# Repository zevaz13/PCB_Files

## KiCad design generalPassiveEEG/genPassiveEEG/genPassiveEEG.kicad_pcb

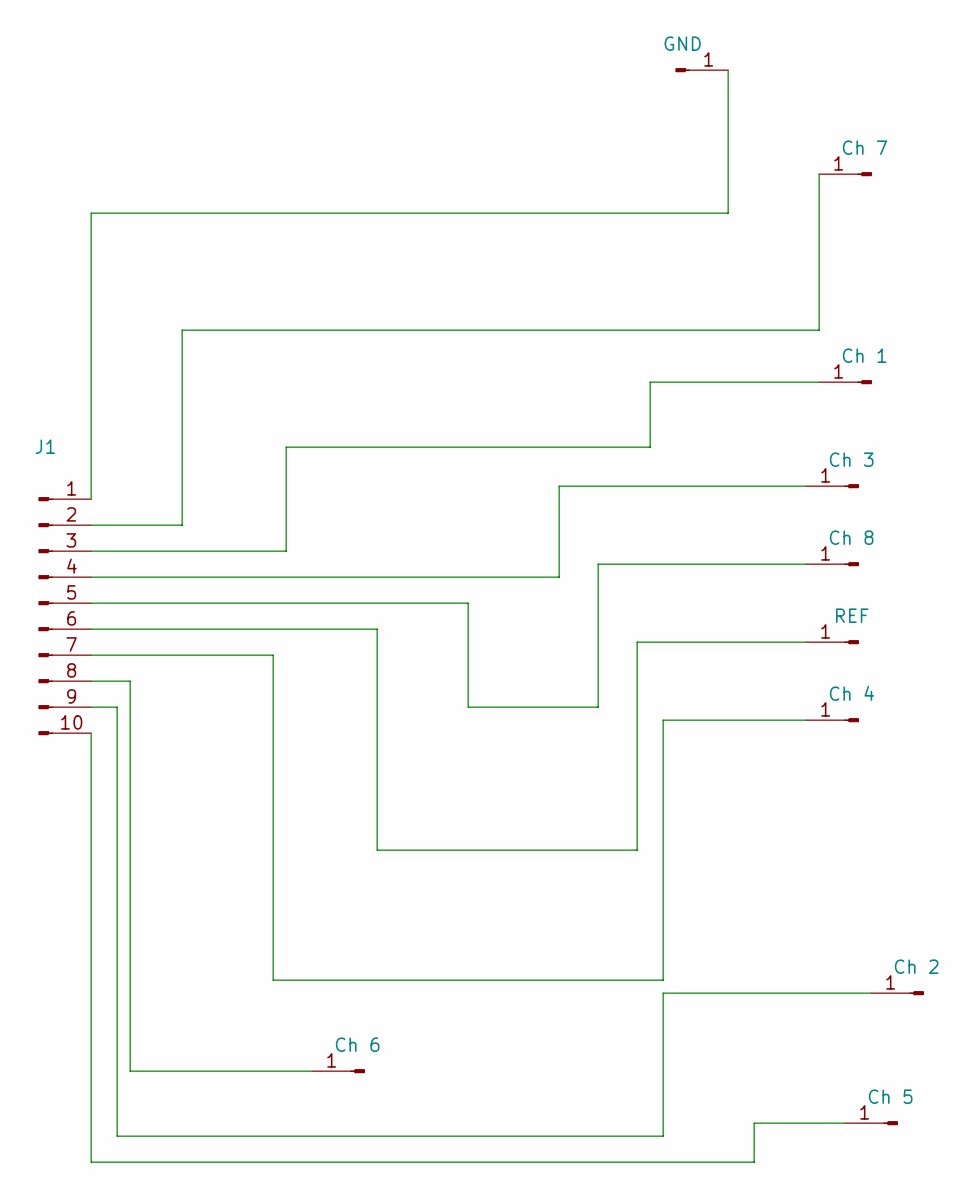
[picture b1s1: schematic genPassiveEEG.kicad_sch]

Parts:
J1: Conn_01x10_Pin; PinHeader_1x10_P2.54mm_Vertical
J2: Ch 7; PinHeader_1x01_P2.54mm_Vertical
J3: Ch 1; PinHeader_1x01_P2.54mm_Vertical
J4: Ch 3; PinHeader_1x01_P2.54mm_Vertical
J5: Ch 8; PinHeader_1x01_P2.54mm_Vertical
J6: REF; PinHeader_1x01_P2.54mm_Vertical
J7: Ch 4; PinHeader_1x01_P2.54mm_Vertical
J8: Ch 6; PinHeader_1x01_P2.54mm_Vertical
J9: Ch 2; PinHeader_1x01_P2.54mm_Vertical
J10: Ch 5; PinHeader_1x01_P2.54mm_Vertical
J12: GND; PinHeader_1x01_P2.54mm_Vertical

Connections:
unnamed: J1.1, J12.1
unnamed: J1.2, J2.1
unnamed: J1.3, J3.1
unnamed: J1.4, J4.1
unnamed: J1.5, J5.1
unnamed: J1.6, J6.1
unnamed: J1.7, J7.1
unnamed: J1.8, J8.1
unnamed: J1.9, J9.1
unnamed: J1.10, J10.1

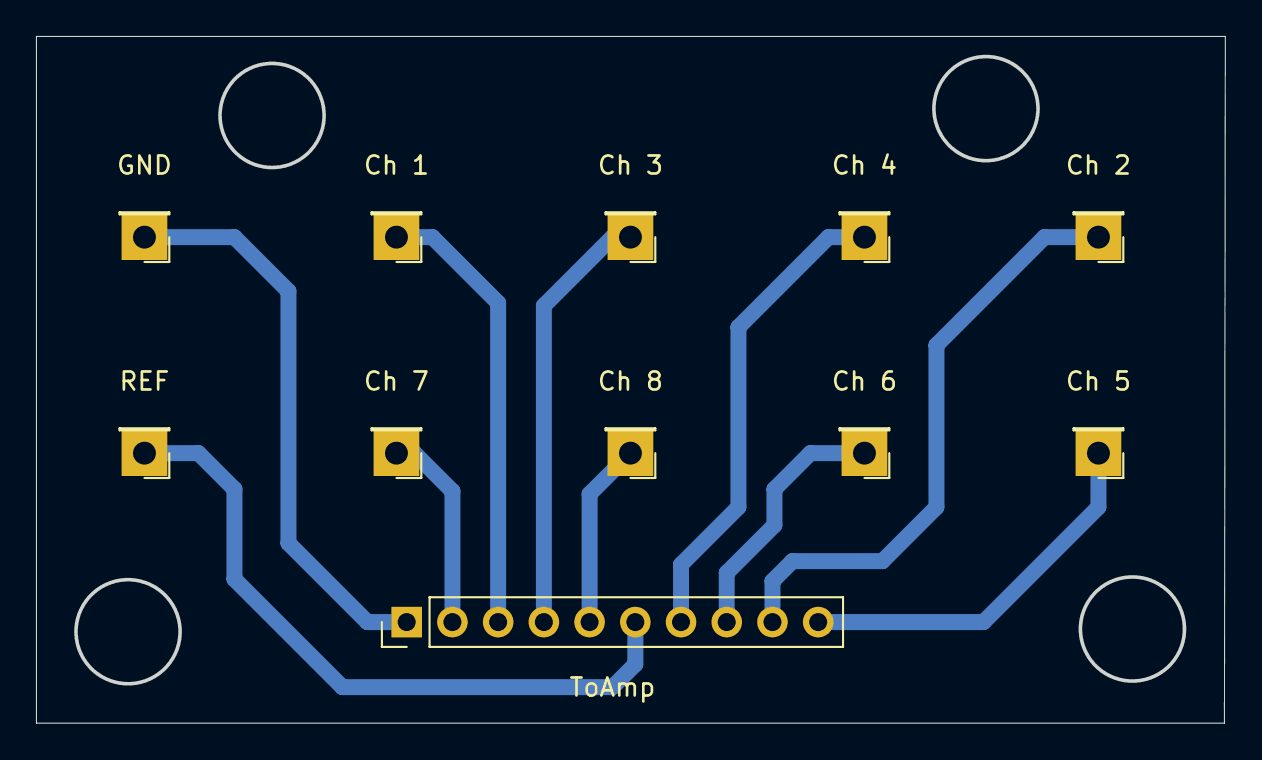
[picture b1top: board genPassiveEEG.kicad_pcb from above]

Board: 2 copper layers, 66.0 x 38.1 mm, 11 parts (0 on the bottom side), 10 nets.

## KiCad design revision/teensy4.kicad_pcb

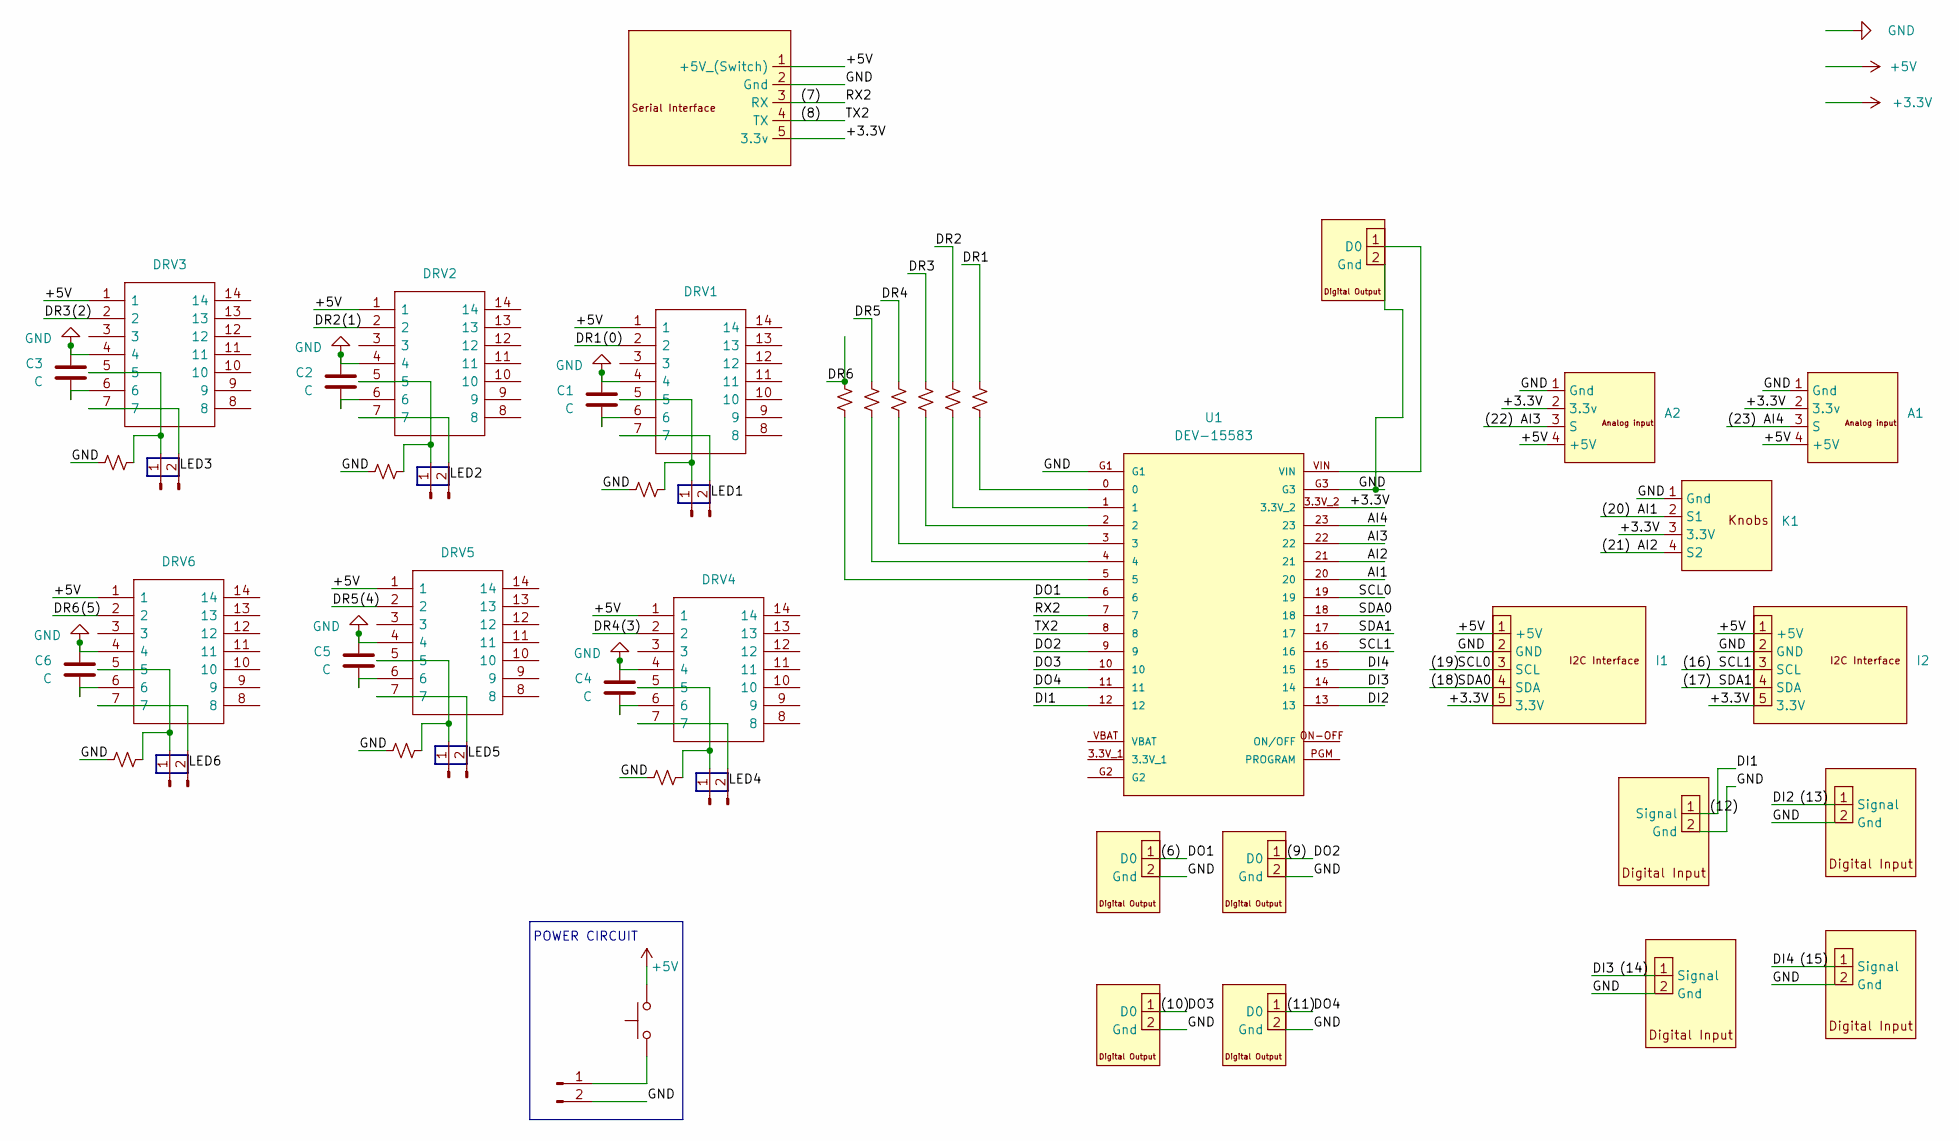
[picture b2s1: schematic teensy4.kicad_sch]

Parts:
A1, A2: FanPinHeader_1x04_P2.54mm_Vertical
C1, C2, C3, C4, C5, C6: C; C_Axial_L3.8mm_D2.6mm_P7.50mm_Horizontal
DI1, DI2, DI3, DI4: PhoenixContact_MSTBVA_2,5_2-G-5,08_1x02_P5.08mm_Vertical
DO1, DO2, DO3, DO4, DO5: PhoenixContact_MSTBVA_2,5_2-G-5,08_1x02_P5.08mm_Vertical
DRV1: DRV1; PA0186; Manufacturer_Part_Number PA0186; Mouser Part Number 910-PA0186
DRV2: DRV2; PA0186; Manufacturer_Part_Number PA0186; Mouser Part Number 910-PA0186
DRV3: DRV3; PA0186; Manufacturer_Part_Number PA0186; Mouser Part Number 910-PA0186
DRV4: DRV4; PA0186; Manufacturer_Part_Number PA0186; Mouser Part Number 910-PA0186
DRV5: DRV5; PA0186; Manufacturer_Part_Number PA0186; Mouser Part Number 910-PA0186
DRV6: DRV6; PA0186; Manufacturer_Part_Number PA0186; Mouser Part Number 910-PA0186
I1, I2: PinHeader_1x05_P2.54mm_Vertical
K1: FanPinHeader_1x04_P2.54mm_Vertical
L1, L2, L3, L4, L5, L6: Conn_01x02_Pin; TerminalBlock_MaiXu_MX126-5.0-02P_1x02_P5.00mm
Power1: Conn_01x02_Pin; TerminalBlock_MaiXu_MX126-5.0-02P_1x02_P5.00mm
RD1, RD2, RD3, RD4, RD5, RD6: R_Small_US; R_Axial_DIN0414_L11.9mm_D4.5mm_P15.24mm_Horizontal
RT0, RT1, RT2, RT3, RT4, RT5: R_Small_US; R_Axial_DIN0207_L6.3mm_D2.5mm_P10.16mm_Horizontal
S1: PinHeader_1x05_P2.54mm_Vertical
SW1: SW_Push; TerminalBlock_MaiXu_MX126-5.0-02P_1x02_P5.00mm
U1: DEV-15583; MODULE_DEV-15583

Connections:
+3.3V: A1.2 (3.3v), A2.2 (3.3v), I1.5 (3.3V), I2.5 (3.3V), K1.3 (3.3V), S1.5 (3.3v), U1.3.3V_2; also elsewhere on the board
+5V: A1.4 (+5V), A2.4 (+5V), DRV1.1, DRV2.1, DRV3.1, DRV4.1, DRV5.1, DRV6.1, I1.1 (+5V), I2.1 (+5V), S1.1 (+5V_(Switch)), SW1.2; also elsewhere on the board
/(0): DRV1.2, RT0.1
/(1): DRV2.2, RT1.1
/(2): DRV3.2, RT2.1
/(3): DRV4.2, RT3.1
/(4): DRV5.2, RT4.1
/(5): DRV6.2, RT5.1
/(6): DO1.1 (D0), U1.6
/(7): S1.3 (RX), U1.7
/(8): S1.4 (TX), U1.8
/(9): DO2.1 (D0), U1.9
/(10): DO3.1 (D0), U1.10
/(11): DO4.1 (D0), U1.11
/(12): DI1.1 (Signal), U1.12
/(13): DI2.1 (Signal), U1.13
/(14): DI3.1 (Signal), U1.14
/(15): DI4.1 (Signal), U1.15
/(16): I2.3 (SCL), U1.16; also elsewhere on the board
/(17): I2.4 (SDA), U1.17; also elsewhere on the board
/(18): I1.4 (SDA), U1.18; also elsewhere on the board
/(19): I1.3 (SCL), U1.19; also elsewhere on the board
/(20): K1.2 (S1), U1.20
/(21): K1.4 (S2), U1.21
/(22): A2.3 (S), U1.22
/(23): A1.3 (S), U1.23
GND: A1.1 (Gnd), A2.1 (Gnd), C1.1, C2.1, C3.1, C4.1, C5.1, C6.1, DI1.2 (Gnd), DI2.2 (Gnd), DI3.2 (Gnd), DI4.2 (Gnd), DO1.2 (Gnd), DO2.2 (Gnd), DO3.2 (Gnd), DO4.2 (Gnd), DO5.2 (Gnd), DRV1.4, DRV2.4, DRV3.4, DRV4.4, DRV5.4, DRV6.4, I1.2 (GND), I2.2 (GND), K1.1 (Gnd), Power1.2, RD1.1, RD2.1, RD3.1, RD4.1, RD5.1, RD6.1, S1.2 (Gnd), U1.G1, U1.G3; also elsewhere on the board
unnamed: C1.2, DRV1.6
unnamed: C2.2, DRV2.6
unnamed: C3.2, DRV3.6
unnamed: C4.2, DRV4.6
unnamed: C5.2, DRV5.6
unnamed: C6.2, DRV6.6
unnamed: DO5.1 (D0), U1.VIN
unnamed: DRV1.5, L1.1, RD1.2
unnamed: DRV1.7, L1.2
unnamed: DRV2.5, L2.1, RD2.2
unnamed: DRV2.7, L2.2
unnamed: DRV3.5, L3.1, RD3.2
unnamed: DRV3.7, L3.2
unnamed: DRV4.5, L4.1, RD4.2
unnamed: DRV4.7, L4.2
unnamed: DRV5.5, L5.1, RD5.2
unnamed: DRV5.7, L5.2
unnamed: DRV6.5, L6.1, RD6.2
unnamed: DRV6.7, L6.2
unnamed: Power1.1, SW1.1
unnamed: RT0.2, U1.0
unnamed: RT1.2, U1.1
unnamed: RT2.2, U1.2
unnamed: RT3.2, U1.3
unnamed: RT4.2, U1.4
unnamed: RT5.2, U1.5

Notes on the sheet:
POWER CIRCUIT

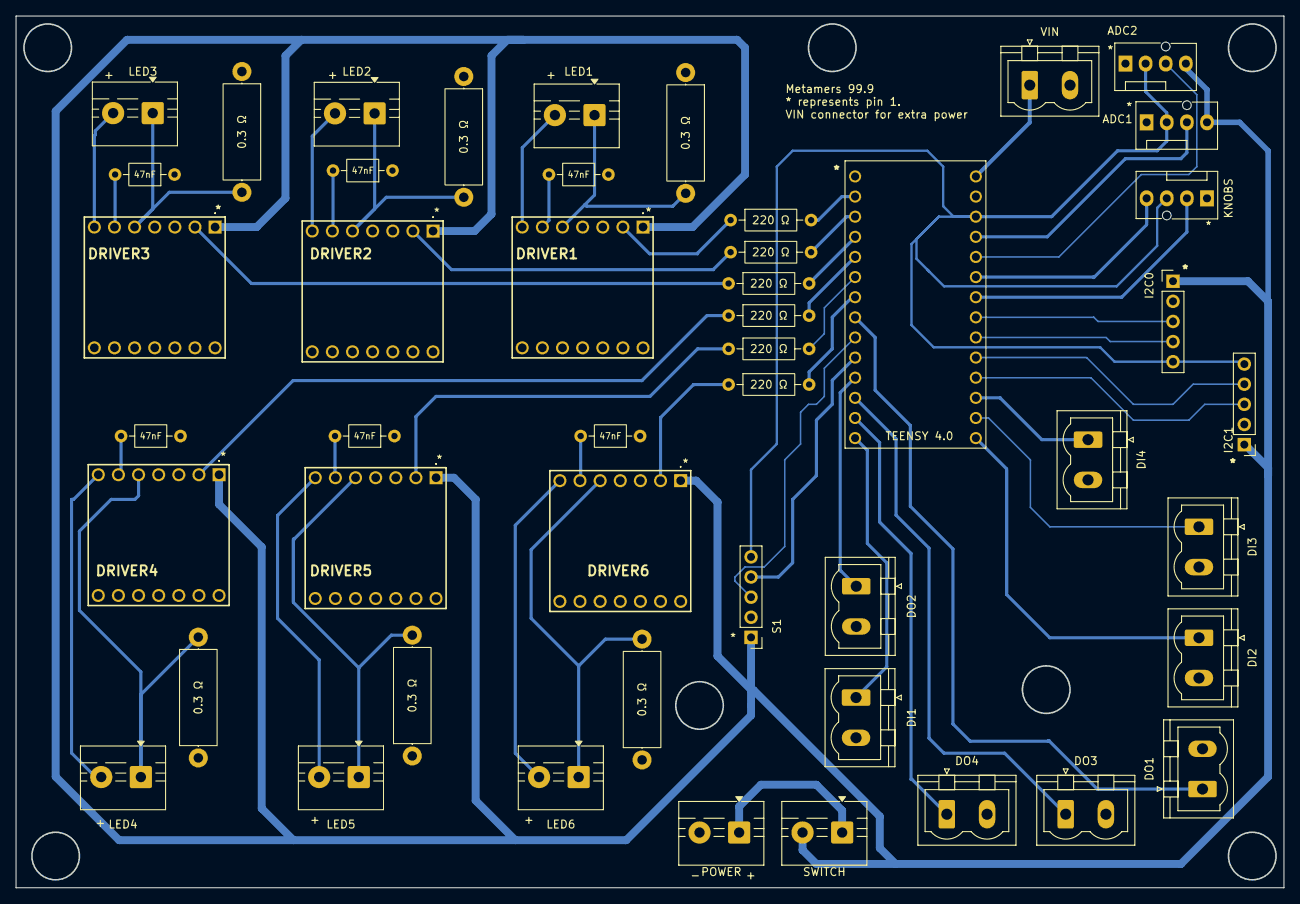
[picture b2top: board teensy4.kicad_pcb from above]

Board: 2 copper layers, 160.0 x 110.0 mm, 48 parts (0 on the bottom side), 53 nets.

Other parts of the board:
I2C0, I2C1: PinHeader_1x05_P2.54mm_Vertical

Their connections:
+3.3V: I2C0.5 (3.3V), I2C1.5 (3.3V); also elsewhere on the board
+5V: I2C0.1 (+5V), I2C1.1 (+5V); also elsewhere on the board
/(16): I2C1.3 (SCL); also elsewhere on the board
/(17): I2C1.4 (SDA); also elsewhere on the board
/(18): I2C0.4 (SDA); also elsewhere on the board
/(19): I2C0.3 (SCL); also elsewhere on the board
GND: I2C0.2 (GND), I2C1.2 (GND); also elsewhere on the board
